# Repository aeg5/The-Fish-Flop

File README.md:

# The-Fish-Flop
This is a PCB for Hack Club Solder! It's a simple flip flop circuit that's fish shaped. The LED can be toggled with the set and reset buttons. My slack username is ag5.

## Schematic

## PCB

## BOM
- 1 battery holder
- 1 LED
- 2 NPN transistors
- 2 330 resistors
- 2 1k resistors 
- 2 2k resistors
- 2 100k resistors
- 2 push buttons

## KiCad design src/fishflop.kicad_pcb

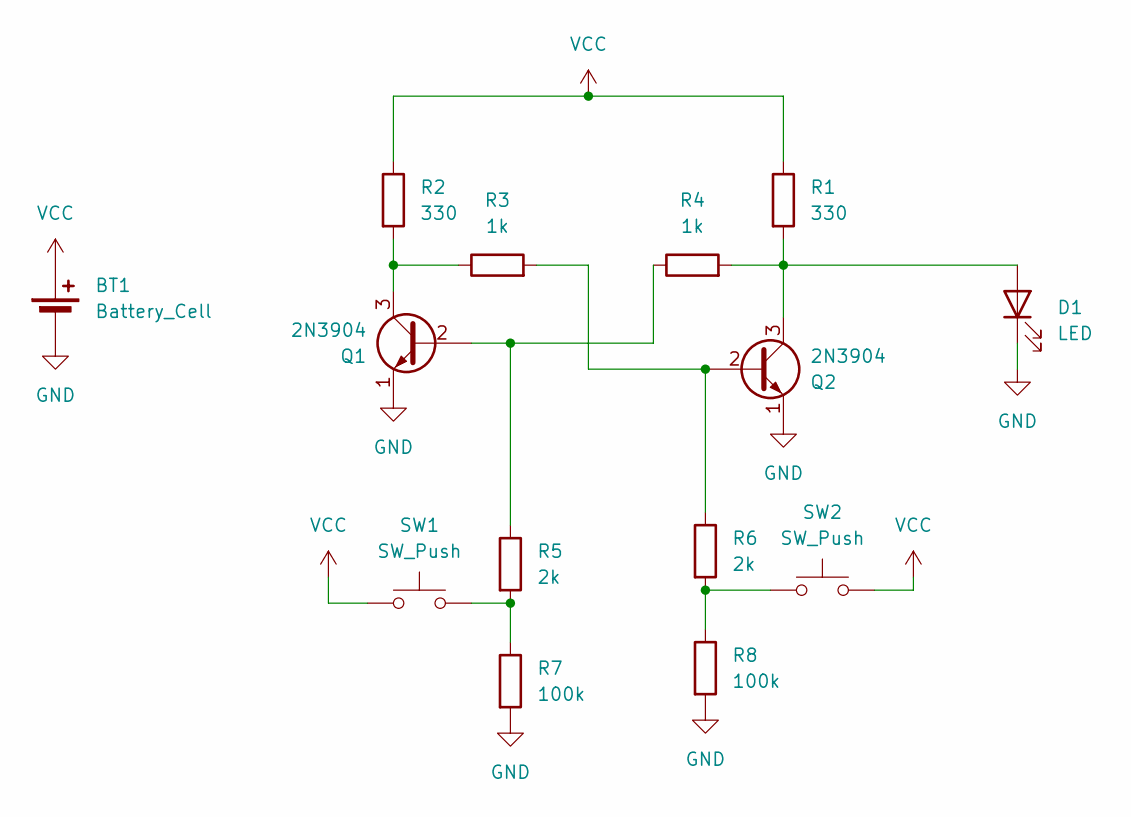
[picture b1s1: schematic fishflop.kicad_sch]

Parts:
BT1: Battery_Cell; BatteryHolder_Keystone_3034_1x20mm
D1: LED; LED_D5.0mm
Q1, Q2: 2N3904; TO-92L_HandSolder
R1, R2: 330; R_Axial_DIN0207_L6.3mm_D2.5mm_P7.62mm_Horizontal
R3, R4: 1k; R_Axial_DIN0207_L6.3mm_D2.5mm_P7.62mm_Horizontal
R5, R6: 2k; R_Axial_DIN0207_L6.3mm_D2.5mm_P7.62mm_Horizontal
R7, R8: 100k; R_Axial_DIN0207_L6.3mm_D2.5mm_P7.62mm_Horizontal
SW1, SW2: SW_Push; SW_PUSH_6mm

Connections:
GND: BT1.2 (-), D1.1 (K), Q1.1 (E), Q2.1 (E), R7.2, R8.2
unnamed: D1.2 (A), Q2.3 (C), R1.2, R4.2
unnamed: Q1.2 (B), R4.1, R5.1
unnamed: Q1.3 (C), R2.2, R3.1
unnamed: Q2.2 (B), R3.2, R6.1
unnamed: R5.2, R7.1, SW1.2
unnamed: R6.2, R8.1, SW2.1
VCC: BT1.1 (+), R1.1, R2.1, SW1.1, SW2.2

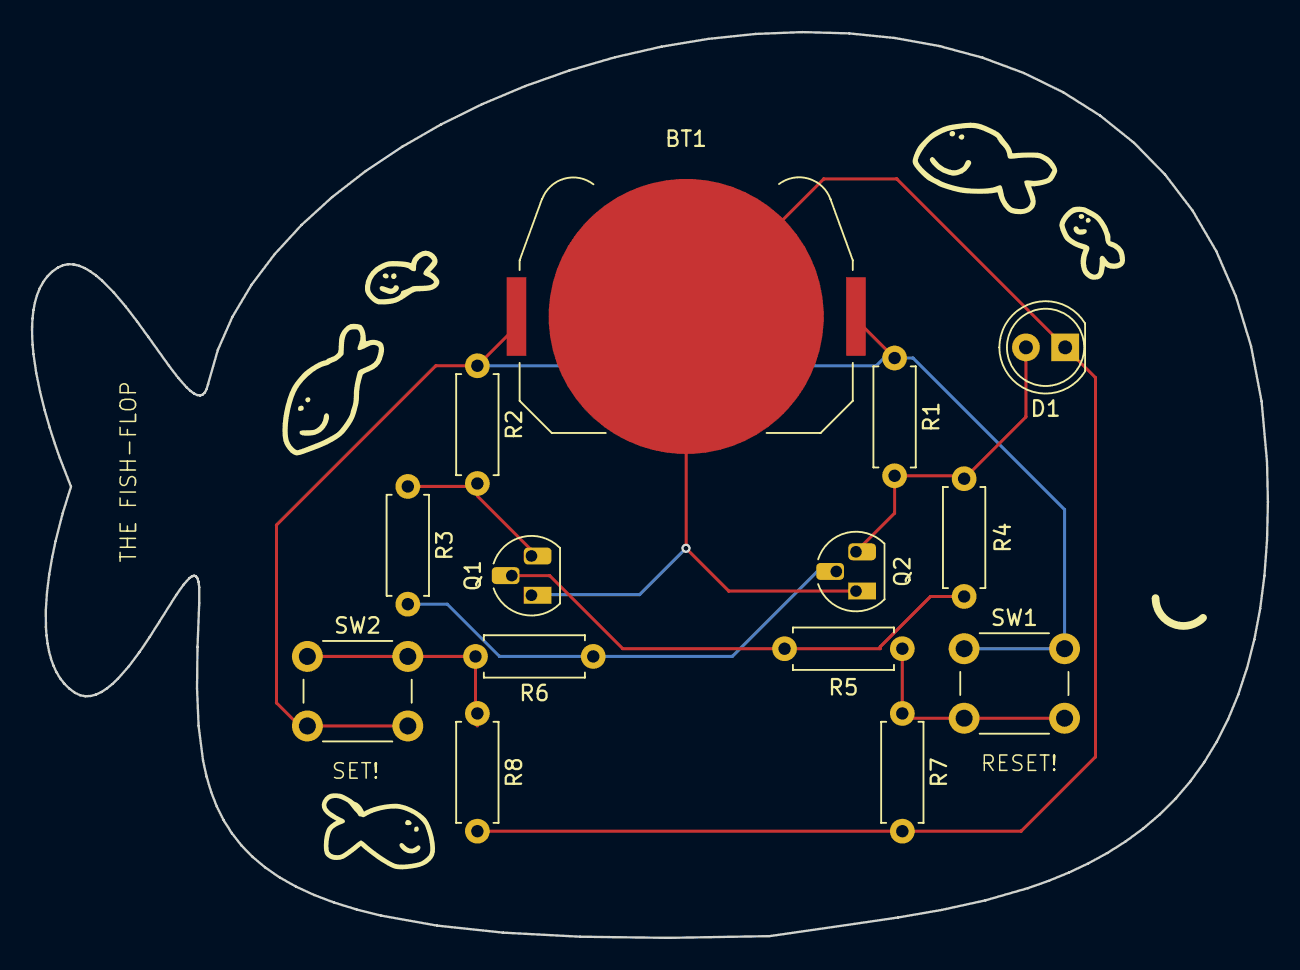
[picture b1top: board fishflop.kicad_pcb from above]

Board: 2 copper layers, 80.0 x 58.6 mm, 14 parts (0 on the bottom side), 8 nets.

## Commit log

2025-05-26 Add src
2025-05-26 Added files
